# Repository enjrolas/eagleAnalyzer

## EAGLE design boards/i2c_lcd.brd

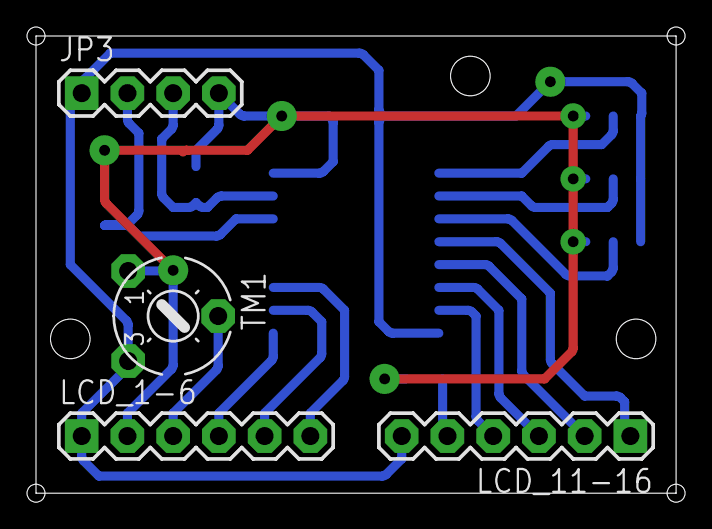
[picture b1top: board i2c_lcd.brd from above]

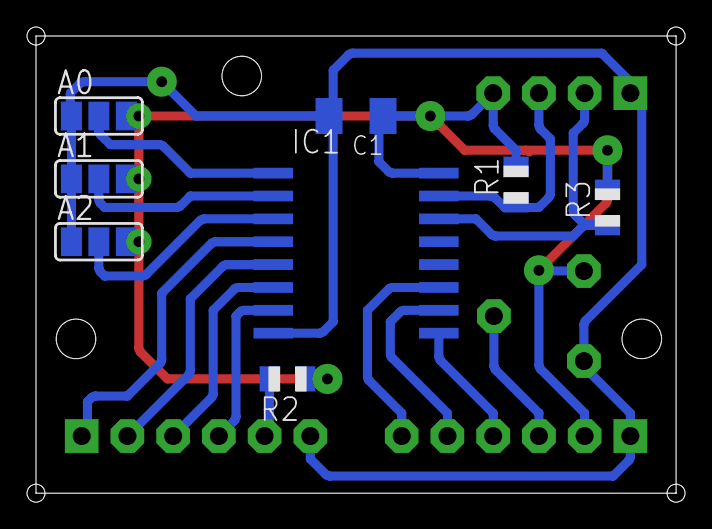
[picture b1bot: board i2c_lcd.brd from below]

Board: 2 copper layers, 35.6 x 25.4 mm, 12 parts (8 on the bottom side), 16 nets.

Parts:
A0, A1, A2: SJ_2
C1: 0.1uF; C1206K
IC1: PCF8574T; SO16W
JP3: 1X04
LCD_1-6, LCD_11-16: 1X06
R1, R3: 10k; R0805
R2: 100; R0805
TM1: 1K; 6MM

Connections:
A0: A0.2, IC1.1
A1: A1.2, IC1.2
A2: A2.2, IC1.3
ANODE: LCD_11-16.5, R2.2
CONTR: LCD_1-6.3, TM1.S
DB4: IC1.4, LCD_11-16.1
DB5: IC1.5, LCD_11-16.2
DB6: IC1.6, LCD_11-16.3
DB7: IC1.7, LCD_11-16.4
ENABLE: IC1.11, LCD_1-6.6
GND: A0.1, A1.1, A2.1, C1.2, IC1.8, JP3.1, LCD_1-6.1, LCD_11-16.6, TM1.E
RS: IC1.9, LCD_1-6.4
RW: IC1.10, LCD_1-6.5
SCL: IC1.14, JP3.2, R3.1
SDA: IC1.15, JP3.3, R1.1
VCC: A0.3, A1.3, A2.3, C1.1, IC1.16, JP3.4, LCD_1-6.2, R1.2, R2.1, R3.2, TM1.A

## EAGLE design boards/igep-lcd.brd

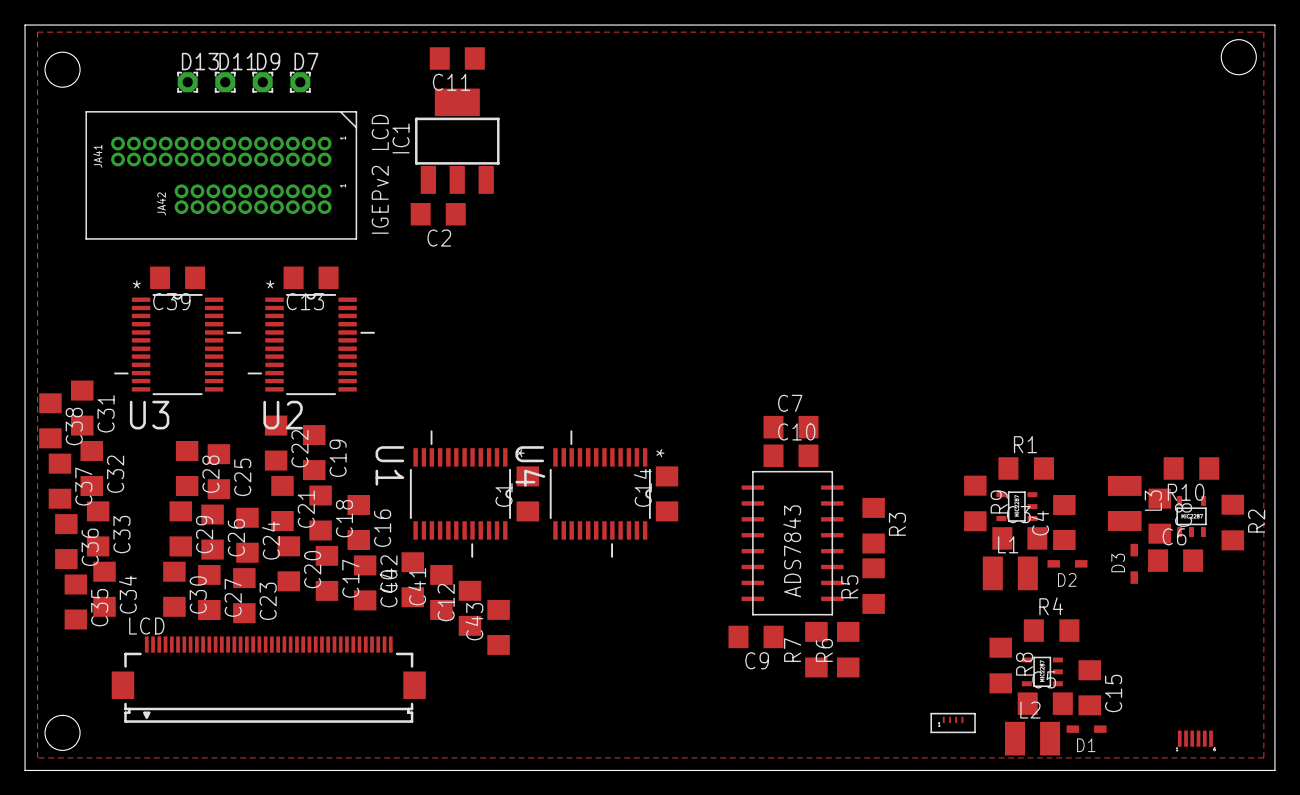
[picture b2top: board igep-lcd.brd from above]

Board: 2 copper layers, 99.9 x 59.6 mm, 76 parts (0 on the bottom side), 110 nets, no tracks yet.

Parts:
C1, C12, C13, C14, C16, C17, C18, C19, C20, C21, C22, C23, C24, C25, C26, C27, C28, C29, C30, C31, C32, C33, C34, C35, C36, C37, C38, C39, C40, C41, C42, C43: 100nF; C1206
C2: 22uF; C1206
C3, C5, C8: 1uF; C1206
C4, C6, C15: 0.22uF; C1206
C7, C11: 10uF; C1206
C9, C10: 0.1uF; C1206
D1, D2, D3: CMDSH-3; SOD323
D7, D9, D11, D13: 1,6/0,8
IC1: LM1117IMPX-3.3; SOT223
L1, L2, L3: 10uH; R1210
LCD: FH12-40S-0.5SH
R1, R2, R4: 5.1; R1206
R3, R5, R6, R7, R8, R9, R10: 0; R1206
U1, U2, U3, U4: SN74LVC8T245PW; SOP65P640X120-24N
U$1: IGEP_LCD
U$2, U$3, U$4: MIC2287
U$5: LCD_BL
U$6: ADS7843
U$7: TS_CON

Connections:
DEN: U4.7, U$1.ACBIAS
HSYNC\: U4.10, U$1.HSYNC
IGEP_LCD_DATA0: U1.3, U$1.D0
IGEP_LCD_DATA1: U1.4, U$1.D1
IGEP_LCD_DATA2: U1.5, U$1.D2
IGEP_LCD_DATA3: U1.6, U$1.D3
IGEP_LCD_DATA4: U1.7, U$1.D4
IGEP_LCD_DATA5: U1.8, U$1.D5
IGEP_LCD_DATA6: U1.9, U$1.D6
IGEP_LCD_DATA7: D7.1, U1.10
IGEP_LCD_DATA8: U2.3, U$1.D8
IGEP_LCD_DATA9: D9.1, U2.4
IGEP_LCD_DATA10: U2.5, U$1.D10
IGEP_LCD_DATA11: D11.1, U2.6
IGEP_LCD_DATA12: U2.7, U$1.D12
IGEP_LCD_DATA13: D13.1, U2.8
IGEP_LCD_DATA14: U2.9, U$1.D14
IGEP_LCD_DATA15: U2.10, U$1.D15
IGEP_LCD_DATA16: U3.3, U$1.D16
IGEP_LCD_DATA17: U3.4, U$1.D17
IGEP_LCD_DATA18: U3.5, U$1.D18
IGEP_LCD_DATA19: U3.6, U$1.D19
IGEP_LCD_DATA20: U3.7, U$1.D20
IGEP_LCD_DATA21: U3.8, U$1.D21
IGEP_LCD_DATA22: U3.9, U$1.D22
IGEP_LCD_DATA23: U3.10, U$1.D23
LCD_DATA0: C22.2, LCD.21
LCD_DATA1: C21.2, LCD.22
LCD_DATA2: C20.2, LCD.23
LCD_DATA3: C19.2, LCD.24
LCD_DATA4: C18.2, LCD.25
LCD_DATA5: C17.2, LCD.26
LCD_DATA6: C16.2, LCD.27
LCD_DATA7: C40.2, LCD.28
LCD_DATA8: C30.2, LCD.13
LCD_DATA9: C29.2, LCD.14
LCD_DATA10: C28.2, LCD.15
LCD_DATA11: C27.2, LCD.16
LCD_DATA12: C26.2, LCD.17
LCD_DATA13: C25.2, LCD.18
LCD_DATA14: C23.2, LCD.19
LCD_DATA15: C24.2, LCD.20
LCD_DATA16: C38.2, LCD.5
LCD_DATA17: C37.2, LCD.6
LCD_DATA18: C36.2, LCD.7
LCD_DATA19: C35.2, LCD.8
LCD_DATA20: C34.2, LCD.9
LCD_DATA21: C33.2, LCD.10
LCD_DATA22: C32.2, LCD.11
LCD_DATA23: C31.2, LCD.12
unnamed: U$1.MCSPI1_CLK, U$6.P16
unnamed: C1.2, C2.2, C3.2, C4.2, C5.2, C6.2, C7.2, C8.2, C9.2, C10.2, C11.2, C13.2, C14.2, C15.2, C39.2, IC1.1, LCD.1, LCD.2, LCD.29, LCD.37, LCD.38, R1.1, R2.1, R4.1, U1.11, U1.12, U1.13, U1.22, U2.11, U2.12, U2.13, U2.22, U3.11, U3.12, U3.13, U3.22, U4.11, U4.12, U4.13, U4.22, U$1.GND1, U$1.GND2, U$2.GND, U$3.GND, U$4.GND, U$6.P6
unnamed: R7.1, U$7.TS4
unnamed: U1.1, U1.2, U2.1, U2.2, U3.1, U3.2, U4.1, U4.2, U$1.VIO_1V8
unnamed: C41.1, C41.2, LCD.32, U4.14
unnamed: R6.1, U$7.TS3
unnamed: U$1.MCSPI1_CS0, U$6.P15
unnamed: C15.1, D1.2, L2.2, U$2.SW
unnamed: C12.1, C12.2, LCD.33, U4.15
unnamed: C42.1, C42.2, LCD.30, U4.16
unnamed: C43.1, C43.2, LCD.34, U4.17
unnamed: R5.1, U$7.TS2
unnamed: D1.1, U$5.VLED_A1
unnamed: R4.2, U$2.FB, U$5.VLED_C1
unnamed: C4.1, D2.2, L1.2, U$3.SW
unnamed: D2.1, U$5.VLED_A2
unnamed: R1.2, U$3.FB, U$5.VLED_C2
unnamed: R3.1, U$7.TS1
unnamed: R10.1, U$4.EN
unnamed: U$1.TS_NPEN_IRQ, U$6.P11
unnamed: C6.1, D3.2, L3.2, U$4.SW
unnamed: D3.1, U$5.VLED_A3
unnamed: R2.2, U$4.FB, U$5.VLED_C3
unnamed: R9.1, U$3.EN
unnamed: U$1.TS_ENVVDD, U$6.P13
unnamed: U$1.MCSPI1_SIMO, U$6.P14
unnamed: U$1.MCSPI1_SOMI, U$6.P12
unnamed: R8.1, U$2.EN
unnamed: R3.2, U$6.P5
unnamed: C38.1, U3.21
unnamed: R5.2, U$6.P4
unnamed: C37.1, U3.20
unnamed: R6.2, U$6.P3
unnamed: R7.2, U$6.P2
unnamed: C3.1, C5.1, C7.1, C8.1, C9.1, C10.1, C11.1, IC1.3, L1.1, L2.1, L3.1, R8.2, R9.2, R10.2, U$1.DC_5V, U$2.VIN, U$3.VIN, U$4.VIN, U$6.P1, U$6.P9, U$6.P10
unnamed: C1.1, C2.1, C13.1, C14.1, C39.1, IC1.2, LCD.3, LCD.4, LCD.31, U1.23, U1.24, U2.23, U2.24, U3.23, U3.24, U4.23, U4.24
unnamed: C36.1, U3.19
unnamed: C35.1, U3.18
unnamed: C34.1, U3.17
unnamed: C33.1, U3.16
unnamed: C32.1, U3.15
unnamed: C31.1, U3.14
unnamed: C30.1, U2.21
unnamed: C29.1, U2.20
unnamed: C28.1, U2.19
unnamed: C27.1, U2.18
unnamed: C26.1, U2.17
unnamed: C25.1, U2.16
unnamed: C23.1, U2.15
unnamed: C24.1, U2.14
unnamed: C22.1, U1.21
unnamed: C21.1, U1.20
unnamed: C20.1, U1.19
unnamed: C19.1, U1.18
unnamed: C18.1, U1.17
unnamed: C17.1, U1.16
unnamed: C16.1, U1.15
unnamed: C40.1, U1.14
PCLK: U4.8, U$1.PCLK
VSYNC: U4.9, U$1.VSYNC

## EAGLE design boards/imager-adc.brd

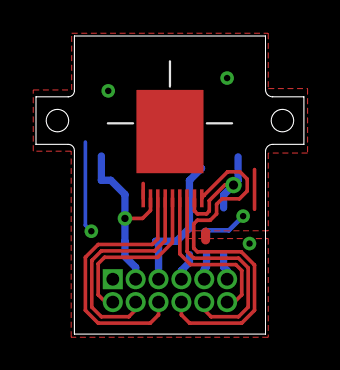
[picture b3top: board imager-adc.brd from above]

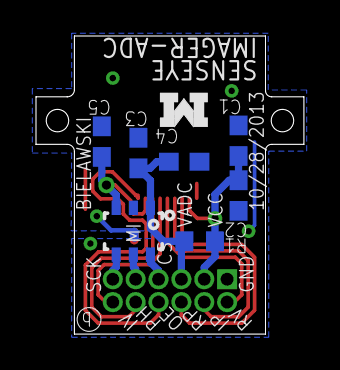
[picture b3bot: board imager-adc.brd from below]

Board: 2 copper layers, 14.9 x 16.6 mm, 10 parts (8 on the bottom side), 13 nets.

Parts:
C1: 1nF; C0603
C2, C3: 0.1uF; C0603
C4: 1uF; C0603
C5: OPTIONAL: 10pF-1nF; C0603
J1: HEADER_12PIN2X6_NOSILK; HEADER2X6/0.05IN_NO_SILK
R1: 0 / UNPOP; R0603
U1: STONYMANDEFAULT_LENS_MOUNT; STONYMAN_DEFAULT_LENS
U2: TI_ADCXX1S101; SOT23-6
U$1: UMICH_SOLID_SMALL; UMICH_SOLID_75MIL

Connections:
ADC-MISO: J1.9, U2.5
ADC-SCLK: J1.11, U2.4
ADC-SS: J1.7, U2.6
ANALOG: C5.1, U1.P$8, U2.3
GND: C1.2, C2.2, C3.2, C4.2, C5.2, J1.1, U1.P$1, U1.P$10, U2.2
INCP: J1.4, U1.P$4
INCV: J1.12, U1.P$6
INPHI: J1.10, U1.P$7
OENABLE: J1.8, U1.P$9
RESP: J1.6, U1.P$3
RESV: J1.2, U1.P$5
V_ADC: C3.1, C4.1, J1.5, R1.1, U2.1
V_STONY: C1.1, C2.1, J1.3, R1.2, U1.P$2

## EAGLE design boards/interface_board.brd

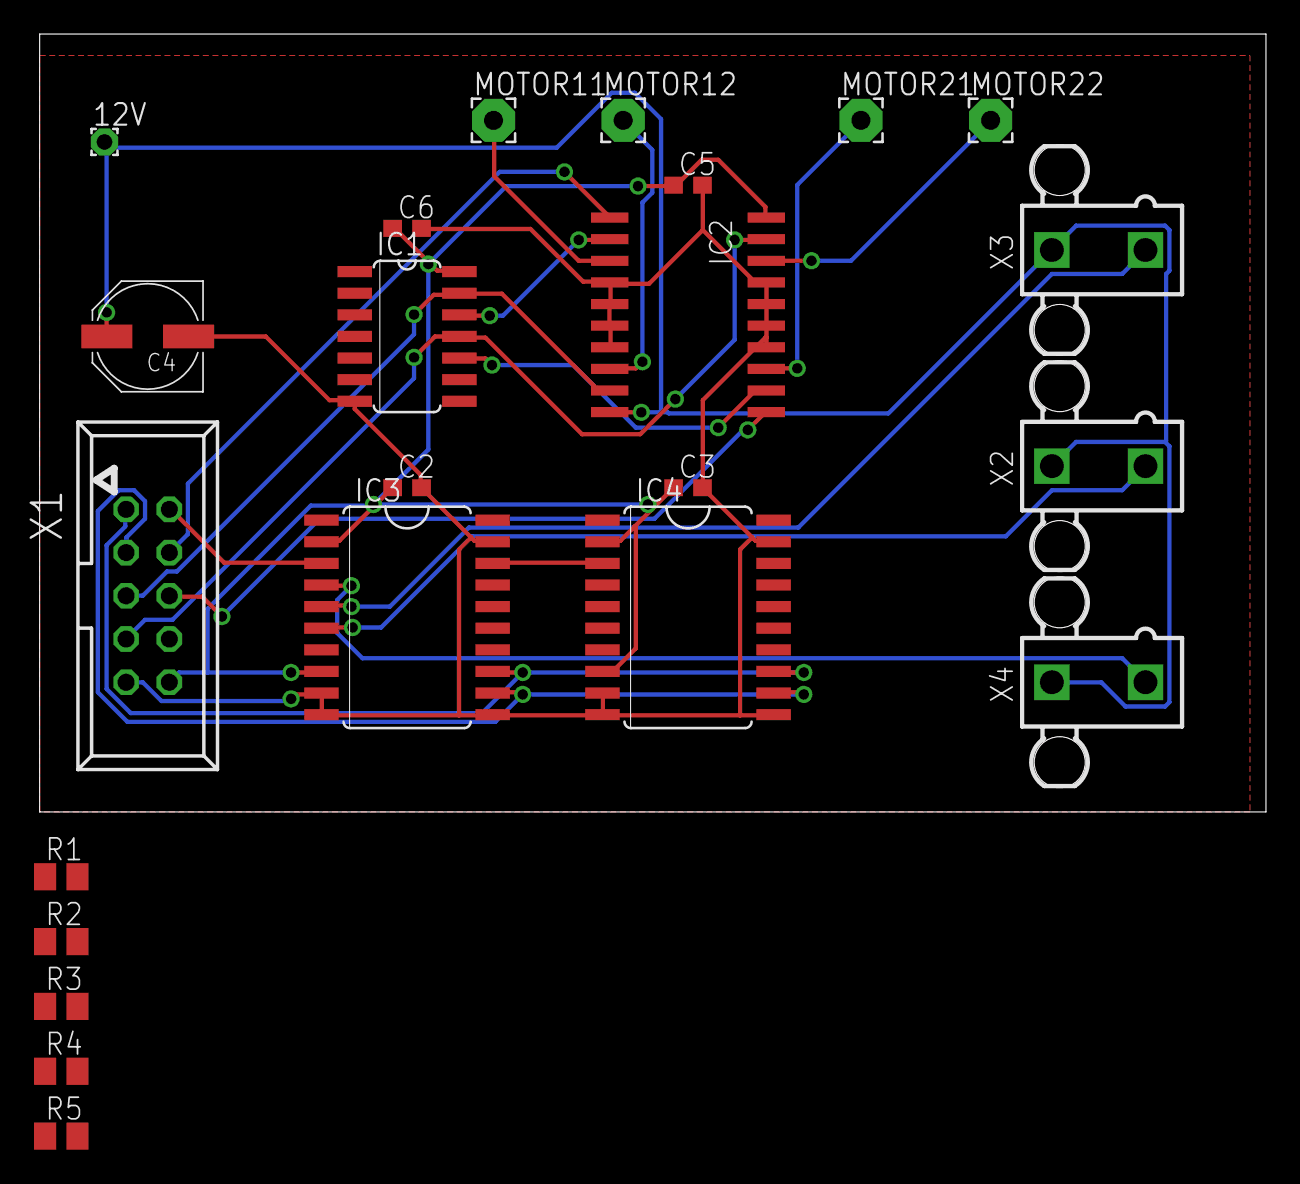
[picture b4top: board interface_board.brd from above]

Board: 2 copper layers, 72.1 x 45.7 mm, 23 parts (0 on the bottom side), 20 nets.

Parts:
12V: 1,6/0,9
C2, C3, C5, C6: 100nF; C0603
C4: 100uF; PANASONIC_D
IC1: 74HCT14D; SO14
IC2: L293DD; SO20
IC3, IC4: TPIC6B596DW; SO20W
MOTOR11, MOTOR12, MOTOR21, MOTOR22: 2,54/1,1
R1, R2, R3, R4, R5: 10k; M0805
X1: 057-010-1
X2, X3, X4: 5566-2

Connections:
+5V: C2.1, C3.1, C5.1, C6.1, IC1.14, IC2.20, IC3.2, IC3.8, IC4.2, IC4.8, X1.10
+12V: 12V.1, C4.+, IC2.10, X2.2, X3.2, X4.2
GND: C2.2, C3.2, C4.-, C5.2, C6.2, IC1.7, IC2.4, IC2.5, IC2.6, IC2.7, IC2.14, IC2.15, IC2.16, IC2.17, IC3.9, IC3.10, IC3.11, IC3.19, IC4.9, IC4.10, IC4.11, IC4.19, R1.2, R2.2, R3.1, R4.2, R5.2, X1.9
unnamed: IC1.13, IC2.9, R5.1, X1.5
unnamed: IC3.4, X4.1
unnamed: IC2.18, MOTOR22.1
unnamed: IC2.1, X1.4
unnamed: IC2.11, X1.6
unnamed: IC2.13, MOTOR21.1
unnamed: IC1.12, IC2.2
unnamed: IC1.10, IC2.12
unnamed: IC2.8, MOTOR12.1
unnamed: IC3.5, X3.1
unnamed: IC2.3, MOTOR11.1
unnamed: IC3.6, X2.1
unnamed: IC1.11, IC2.19, R4.1, X1.7
unnamed: IC3.18, IC4.3
unnamed: IC3.3, R1.1, X1.2
unnamed: IC3.12, IC4.12, R2.1, X1.3
unnamed: IC3.13, IC4.13, R3.2, X1.1

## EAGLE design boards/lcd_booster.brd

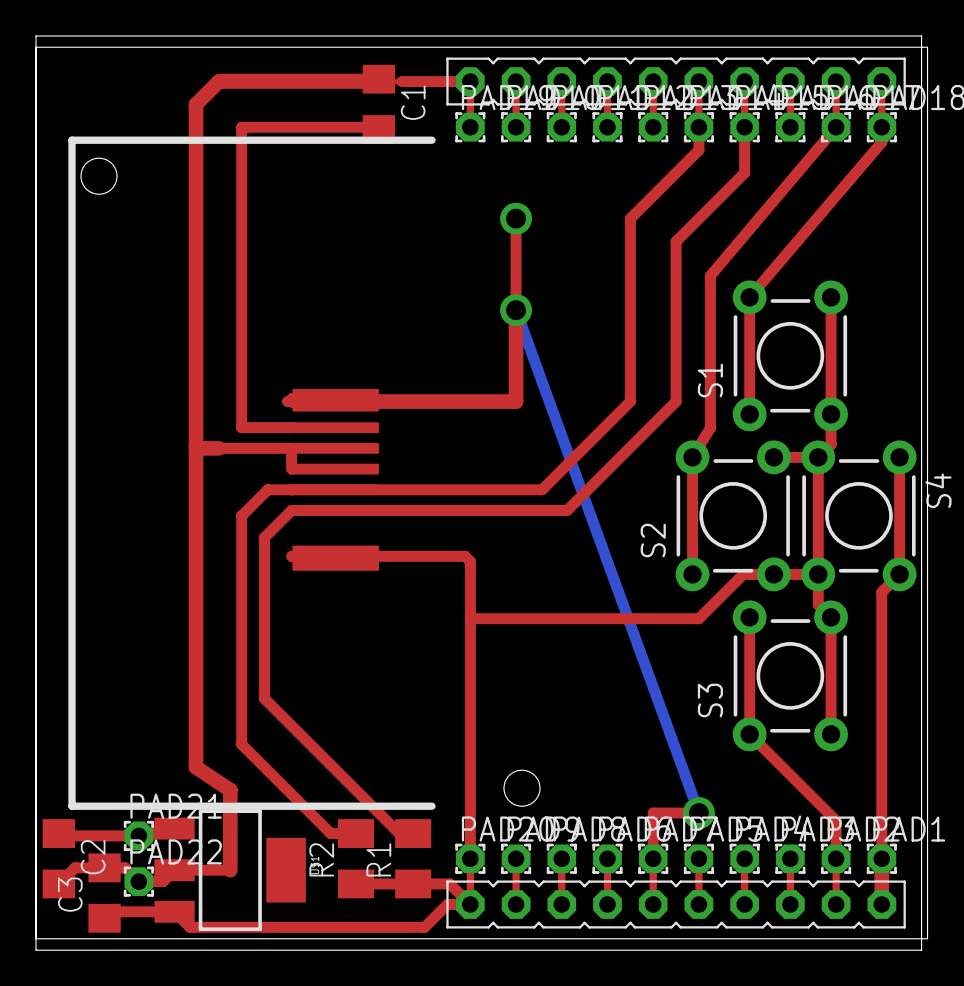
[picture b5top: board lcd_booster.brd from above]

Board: 2 copper layers, 49.2 x 50.8 mm, 34 parts (0 on the bottom side), 22 nets.

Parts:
C1, C2, C3: C1206
PAD1, PAD2, PAD3, PAD4, PAD5, PAD6, PAD7, PAD8, PAD9, PAD10, PAD11, PAD12, PAD13, PAD14, PAD15, PAD16, PAD17, PAD18, PAD19, PAD20, PAD21, PAD22: 1,6/0,9
R1, R2: M1206
S1, S2, S3, S4: TACTILE-PTH
U$1: V_REG_MIC2920; SOT223
U$2: PE9665ARF
U$3: LAUNCHPAD-50MM-LEFT

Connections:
unnamed: PAD1.1, S4.1, S4.2, U$3.P2.2
unnamed: PAD17.1, S2.1, S2.2, U$3.P2.4
unnamed: PAD15.1, R1.2, U$2.SCL, U$3.P1.6
unnamed: PAD14.1, R2.2, U$2.SDA, U$3.P1.7
unnamed: C1.1, C2.2, C3.2, PAD19.1, PAD22.1, U$1.2, U$2.SAO, U$2.VSS, U$3.GND
unnamed: C1.2, U$2.VLCD
unnamed: PAD2.1, S3.1, S3.2, U$3.P2.1
unnamed: PAD7.1, U$2./RES, U$3.P1.3
unnamed: PAD3.1, U$3.P2.0
unnamed: PAD18.1, S1.1, S1.2, U$3.P2.3
unnamed: PAD4.1, U$3.P1.5
unnamed: PAD5.1, U$3.P1.4
unnamed: PAD6.1, U$3.P1.2
unnamed: PAD8.1, U$3.P1.1
unnamed: PAD9.1, U$3.P1.0
unnamed: PAD10.1, U$3.P2.6
unnamed: PAD11.1, U$3.P2.7
unnamed: PAD12.1, U$3.TEST
unnamed: PAD13.1, U$3.RST
unnamed: PAD16.1, U$3.P2.5
unnamed: C3.1, PAD20.1, R1.1, R2.1, S1.3, S1.4, S2.3, S2.4, S3.3, S3.4, S4.3, S4.4, U$1.3, U$2.VDD, U$3.VCC
unnamed: C2.1, PAD21.1, U$1.1

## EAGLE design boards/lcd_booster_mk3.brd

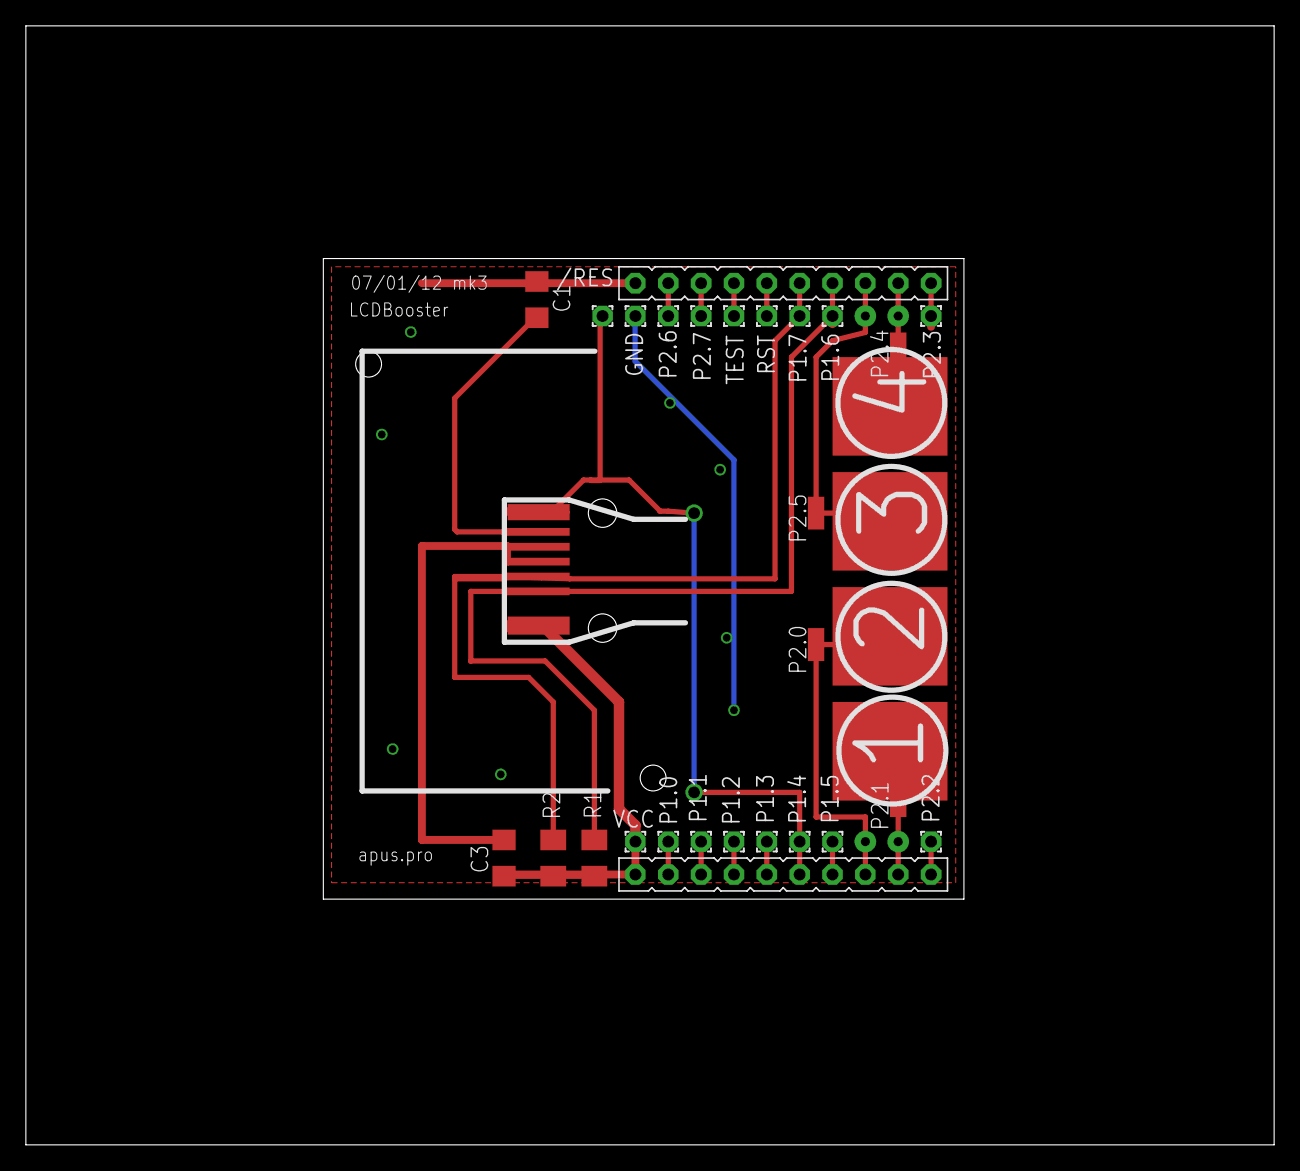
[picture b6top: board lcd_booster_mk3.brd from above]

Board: 2 copper layers, 96.5 x 86.5 mm, 27 parts (0 on the bottom side), 21 nets.

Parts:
/RES: 1,6/0,9
C1, C3: C1206
GND: 1,6/0,9
P1.0, P1.1, P1.2, P1.3, P1.4, P1.5, P1.6, P1.7, P2.2, P2.3, P2.6, P2.7: 1,6/0,9
P2.0, P2.1, P2.4, P2.5: SMD1,27-2,54
R1, R2: M1206
RST: 1,6/0,9
TEST: 1,6/0,9
U$2: PE9665ARF
U$3: LAUNCHPAD-50MM-LEFT
VCC: 1,6/0,9

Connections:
/RES: /RES.1, P1.4.1, U$2./RES, U$3.P1.4
GND: C1.1, C3.2, GND.1, U$2.SAO, U$2.VSS, U$3.GND
unnamed: P2.2.1, U$3.P2.2
unnamed: P1.3.1, U$3.P1.3
unnamed: P1.0.1, U$3.P1.0
unnamed: P2.1.1, U$3.P2.1
unnamed: C1.2, U$2.VLCD
unnamed: P2.0.1, U$3.P2.0
unnamed: P1.5.1, U$3.P1.5
unnamed: P1.2.1, U$3.P1.2
unnamed: P1.1.1, U$3.P1.1
unnamed: C3.1, R1.1, R2.1, U$2.VDD, U$3.VCC, VCC.1
P1.6: P1.6.1, R1.2, U$2.SCL, U$3.P1.6
P1.7: P1.7.1, R2.2, U$2.SDA, U$3.P1.7
P2.3: P2.3.1, U$3.P2.3
P2.4: P2.4.1, U$3.P2.4
P2.5: P2.5.1, U$3.P2.5
P2.6: P2.6.1, U$3.P2.6
P2.7: P2.7.1, U$3.P2.7
RST: RST.1, U$3.RST
TEST: TEST.1, U$3.TEST

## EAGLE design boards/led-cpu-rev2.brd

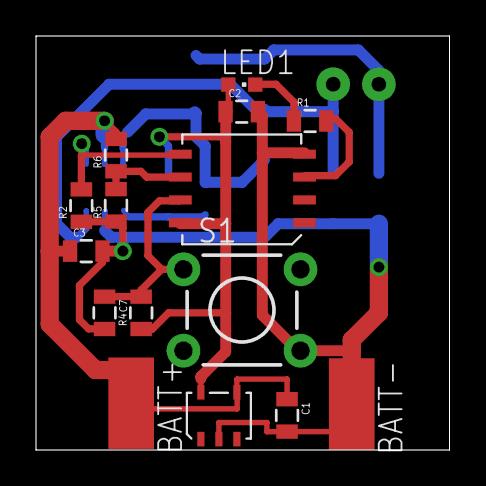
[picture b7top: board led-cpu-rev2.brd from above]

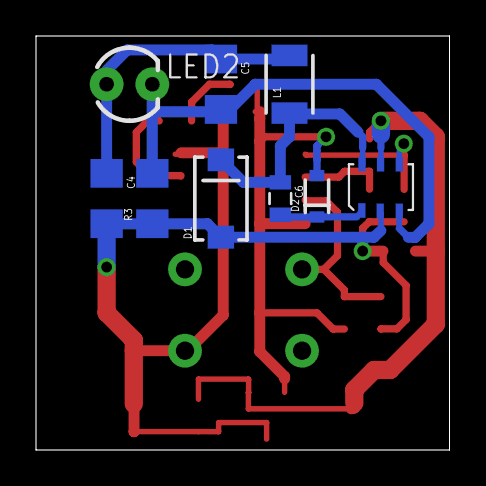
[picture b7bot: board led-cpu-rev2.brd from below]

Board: 2 copper layers, 23.0 x 23.0 mm, 24 parts (9 on the bottom side), 12 nets.

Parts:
BATT+: SMD2,54-5,08
BATT-: SMD2,54-5,08
C1, C3: 10uF, 16v; 0805
C2: 0.1uF; 0805
C4, C5: 1uF; 1206
C6: 10nF; 0805
C7: 1uF; 0805
D1: SMA-DIODE
D2: SOD-323
L1: 4.7uH; 1210
LED1: D1; CHIPLED_0603
LED2: LED3MM
R1: 470; 0805
R2, R4: 10k; 0805
R3: 0.2; 1206
R5: 15k; 0805
R6: 68k; 0805
S1: TACTILE-PTH
U1: TPS71550; SOT-23-5
U2: ATTINY13; WSOIC-8
U$1: LM3405TSOT-6; TSOT-6

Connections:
BATT+: BATT+.1, C1.1, C3.1, R6.2, U1.4, U$1.5
GND: BATT-.1, C1.2, C2.2, C3.2, C4.2, C7.2, D1.A, R2.1, R3.1, R5.1, S1.4, U1.2, U2.4, U$1.2
IND_LED_B: R1.2, U2.3
unnamed: LED1.C, R1.1
unnamed: C5.2, LED2.K, R3.2, U$1.3
unnamed: C6.1, D1.C, L1.1, U$1.6
unnamed: C6.2, D2.1, U$1.1
unnamed: C4.1, C5.1, L1.2, LED2.A
PWM_OUT: R2.2, U2.5, U$1.4
PWR_SW: C7.1, R4.2, S1.1, U2.7
VCC: C2.1, D2.2, LED1.A, R4.1, U1.5, U2.8
VDIV: R5.2, R6.1, U2.6

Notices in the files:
parts and their libraries:
SparkFun-Connectors: Licensing: CC v3.0 Share-Alike You are welcome to use this library for commercial purposes.
